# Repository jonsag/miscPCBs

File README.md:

# miscPCBs

A collection of own designed PCBs.  

## 2PinLCDBackPack

Interface and Arduino to an HD4470 LCD using the I2C protocol.  
Uses an PCF8574 I2C I/O bus expander.  

## 3PinLCDBackpack

Interface an Arduino to an HD4470 LCD with 3 pins instead of 6.  
Using the 74HC595 8-bit shift register with output latches.  

## 8PinLCDBackPack

## FM-Transmitter

A miniaturized FM transmitter.  

## LCDBackPack

The default way to control the HD4470 LCD.  

## medzik TDA2005 Amplifier

A basic amplifier using the 2-channel TDA2005.  

## rotaryToolMotorController

Schematics of a Dremel 3000 motor control.  

## TDA2005-amplifiers

1-channel bridged amplifier using TDA2005.  
2-channel amplifier with tone, balance and loudness control. Also with TDA2005.  

## TDA2005R

An amplifier with PCB layout possible to etch at home.  
Uses TDA2005.  

## Uber I2C LCD Controller Module

Even more control over the LCD.

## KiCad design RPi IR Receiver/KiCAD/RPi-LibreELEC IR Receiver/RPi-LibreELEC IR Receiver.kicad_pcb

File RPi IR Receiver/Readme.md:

# RPi/LibreELEC IR Receiver

## Software

Edit config  

>$ mount -o remount,rw /flash  
>$ nano /flash/config.txt  

Uncomment  'dtoverlay=gpio-ir,gpio_pin=18' so that  

    # uncomment to enable infrared remote receiver connected to GPIO 18
    dtoverlay=gpio-ir,gpio_pin=18

>$ mount -o remount,ro /flash  
>$ reboot  

### If you have a Hauppauge remote

    /storage/.config/rc_maps.cfg  

    /storage/.config/rc_keymaps/hauppauge  

## Testing

To test a different keytable file run  

>$ ir-keytable -c -w /path/to/keytable-file

For example  

>$ ir-keytable -c -w /usr/lib/udev/rc_keymaps/samsung

If the output ends with these lines the protocol is not supported by the IR receiver  

    Invalid protocols selected
    Couldn't change the IR protocols

## Creating own keytable

From [https://wiki.libreelec.tv/configuration/ir-remotes](https://wiki.libreelec.tv/configuration/ir-remotes)  

If you cannot find a working keymap or the current keymap has missing buttons you can create your own.  

Stop Kodi  

>$ systemctl stop kodi  
>$ systemctl stop eventlircd

Run  

>$ ir-keytable

to find out which protocols the receiver driver supports. Look at the 'Supported protocols'  

    Found /sys/class/rc/rc0/ (/dev/input/event1) with:
            Driver gpio-rc-recv, table rc-rc6-mce
            Supported protocols: lirc rc-5 rc-5-sz jvc sony nec sanyo mce_kbd rc-6 sharp xmp
            Enabled protocols: lirc nec rc-6
            Name: gpio_ir_recv
            bus: 25, vendor/product: 0001:0001, version: 0x0100
            Repeat delay = 500 ms, repeat period = 125 ms

Run  

>$ ir-keytable -p \<PROTOCOL\> -t

and press buttons on the remote. If you discover the correct protocol you will see EV_MSC events and the scancode of the button pressed  

    Protocols changed to rc-5
    Testing events. Please, press CTRL-C to abort.
    1503592437.660155: event type EV_MSC(0x04): scancode = 0x101a
    1503592437.660155: event type EV_SYN(0x00).
    1503592437.774129: event type EV_MSC(0x04): scancode = 0x101a
    1503592437.774129: event type EV_SYN(0x00).
    1503592437.921009: event type EV_MSC(0x04): scancode = 0x101a

If you see no events stop ir-keytable with CTRL-C and try another protocol from the list. You can ignore lirc as this is not a real protocol.  

Once you find the correct IR protocol create  

    /storage/.config/rc_keymaps/custom_remote
    
and set the header file. In the example above the protocol is rc-5 so we set  

    # table custom_remote, type: rc-5

Now build the keytable file  

>$ nano /storage/.config/rc_keymaps/custom_remote

Run  

>$ ir-keytable -t

to find out the scancode of each button.  
For each button do the following:  

* Press a button and note the scancode (the 0x… value after scancode:)

* Add a new line with the scancode (including 0x).

* Add the Linux keycode in "quoted" format and separated with a blank.

You can get a list of all supported Linux keycodes via  

>$ irrecord -l | grep ^KEY

but it is easiest to use keycodes listed in the  

    <remote device=“devinput”>
    
section of  

    /usr/share/kodi/system/Lircmap.xml

Once you are finished with the keytable, save the file, stop ir-keytable -t with CTRL-C and then restart it with the keytable file  

>$ ir-keytable -c -w /storage/.config/rc_keymaps/custom_remote

    Read justboom table
    Old keytable cleared
    Wrote 12 keycode(s) to driver
    Protocols changed to rc-5

Now run  

>$ ir-keytable -t

and press buttons  

    Testing events. Please, press CTRL-C to abort.
    1503599395.150849: event type EV_MSC(0x04): scancode = 0x1019
    1503599395.150849: event type EV_KEY(0x01) key_down: KEY_VOLUMEUP(0x0073)
    1503599395.150849: event type EV_SYN(0x00).
    1503599395.264827: event type EV_MSC(0x04): scancode = 0x1019
    1503599395.264827: event type EV_SYN(0x00).
    1503599395.413668: event type EV_MSC(0x04): scancode = 0x1019
    1503599395.413668: event type EV_SYN(0x00).
    1503599395.673626: event type EV_KEY(0x01) key_up: KEY_VOLUMEUP(0x0073)
    1503599395.673626: event type EV_SYN(0x00).

If the test is successful, make the keytable persistent by creating  

    /storage/.config/rc_maps.cfg
    
with the following content:  

    * * custom_remote

Reboot and you should have a working remote in Kodi  

## Links

* [Using an IR Remote with a Raspberry Pi Media Center](https://learn.adafruit.com/using-an-ir-remote-with-a-raspberry-pi-media-center/hardware)
* [Add Infrared Interface to Your Raspberry Pi GPIO](https://www.instructables.com/Add-Infrared-Interface-to-Your-Raspberry-Pi/)
* [How to Send and Receive IR Signals with a Raspberry PiT](https://www.digikey.se/sv/maker/tutorials/2021/how-to-send-and-receive-ir-signals-with-a-raspberry-pi?srsltid=AfmBOorkv28s5m4hSEOjsUYEw9_w3052pLwMHnE4Wjwx3rge6P-vsTNT)
* [TSOP38238  IR-Receiver 38kHz](https://www.electrokit.com/tsop38238-ir-mottagare-38khz)

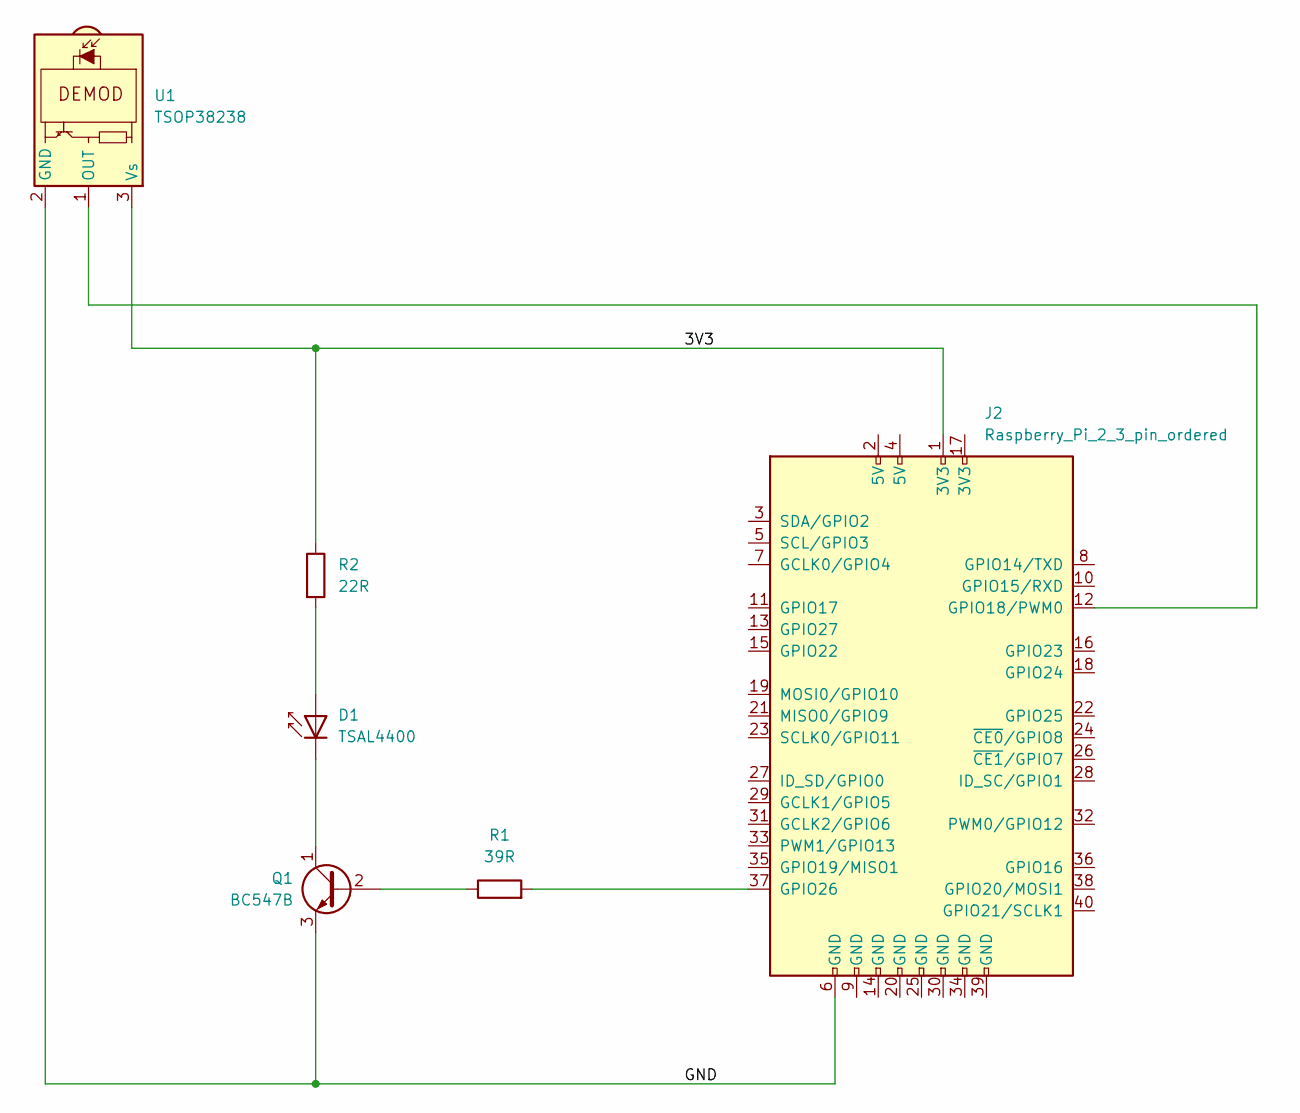
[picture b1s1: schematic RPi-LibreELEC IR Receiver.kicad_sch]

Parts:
D1: TSAL4400; LED_D3.0mm_IRBlack
J2: Raspberry_Pi_2_3_pin_ordered; RaspberryPi_Hat_2x20_pin_GPIO_larger_pads
Q1: BC547B; TO-92_Inline_Wide_large
R1: 39R; R_Axial_DIN0207_L6.3mm_D2.5mm_P10.16mm_Horizontal_large
R2: 22R; R_Axial_DIN0207_L6.3mm_D2.5mm_P10.16mm_Horizontal_large
U1: TSOP38238; Vishay_MINICAST-3Pin

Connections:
/3V3: J2.1 (3V3), R2.1, U1.3 (Vs)
/GND: J2.6 (GND), Q1.3 (E), U1.2 (GND)
unnamed: D1.2 (A), R2.2
unnamed: D1.1 (K), Q1.1 (C)
unnamed: J2.12 (GPIO18/PWM0), U1.1 (OUT)
unnamed: J2.37 (GPIO26), R1.2
unnamed: Q1.2 (B), R1.1

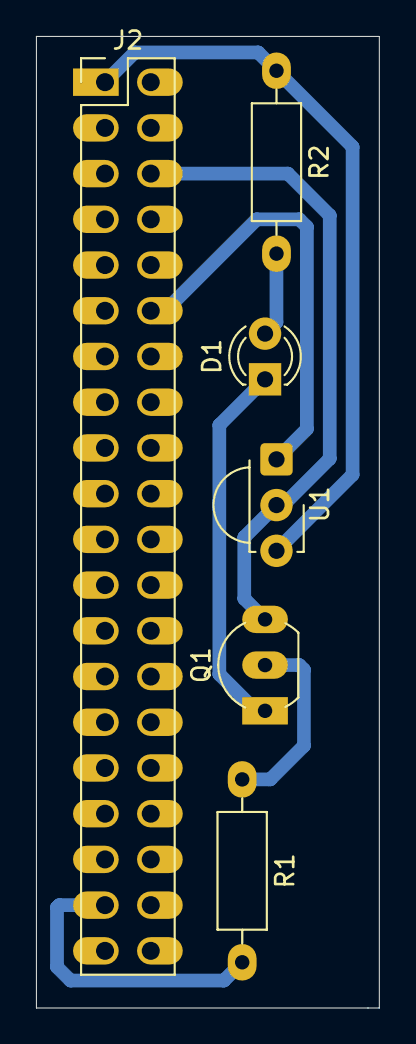
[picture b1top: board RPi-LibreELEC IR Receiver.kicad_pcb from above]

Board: 2 copper layers, 19.0 x 54.0 mm, 6 parts (0 on the bottom side), 7 nets.

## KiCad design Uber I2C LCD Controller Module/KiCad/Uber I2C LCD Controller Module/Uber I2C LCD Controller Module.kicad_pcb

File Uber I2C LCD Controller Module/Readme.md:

# Uber I2C LCD Controller Module

## Links

* [https://www.instructables.com/I2C-LCD-Controller-Module/](https://www.instructables.com/I2C-LCD-Controller-Module/)
* [https://github.com/SteveQuinn1/LiquidCrystal_I2C_PCF8574](https://github.com/SteveQuinn1/LiquidCrystal_I2C_PCF8574)
* [https://github.com/SteveQuinn1/MCP4561_DIGI_POT](https://github.com/SteveQuinn1/MCP4561_DIGI_POT)

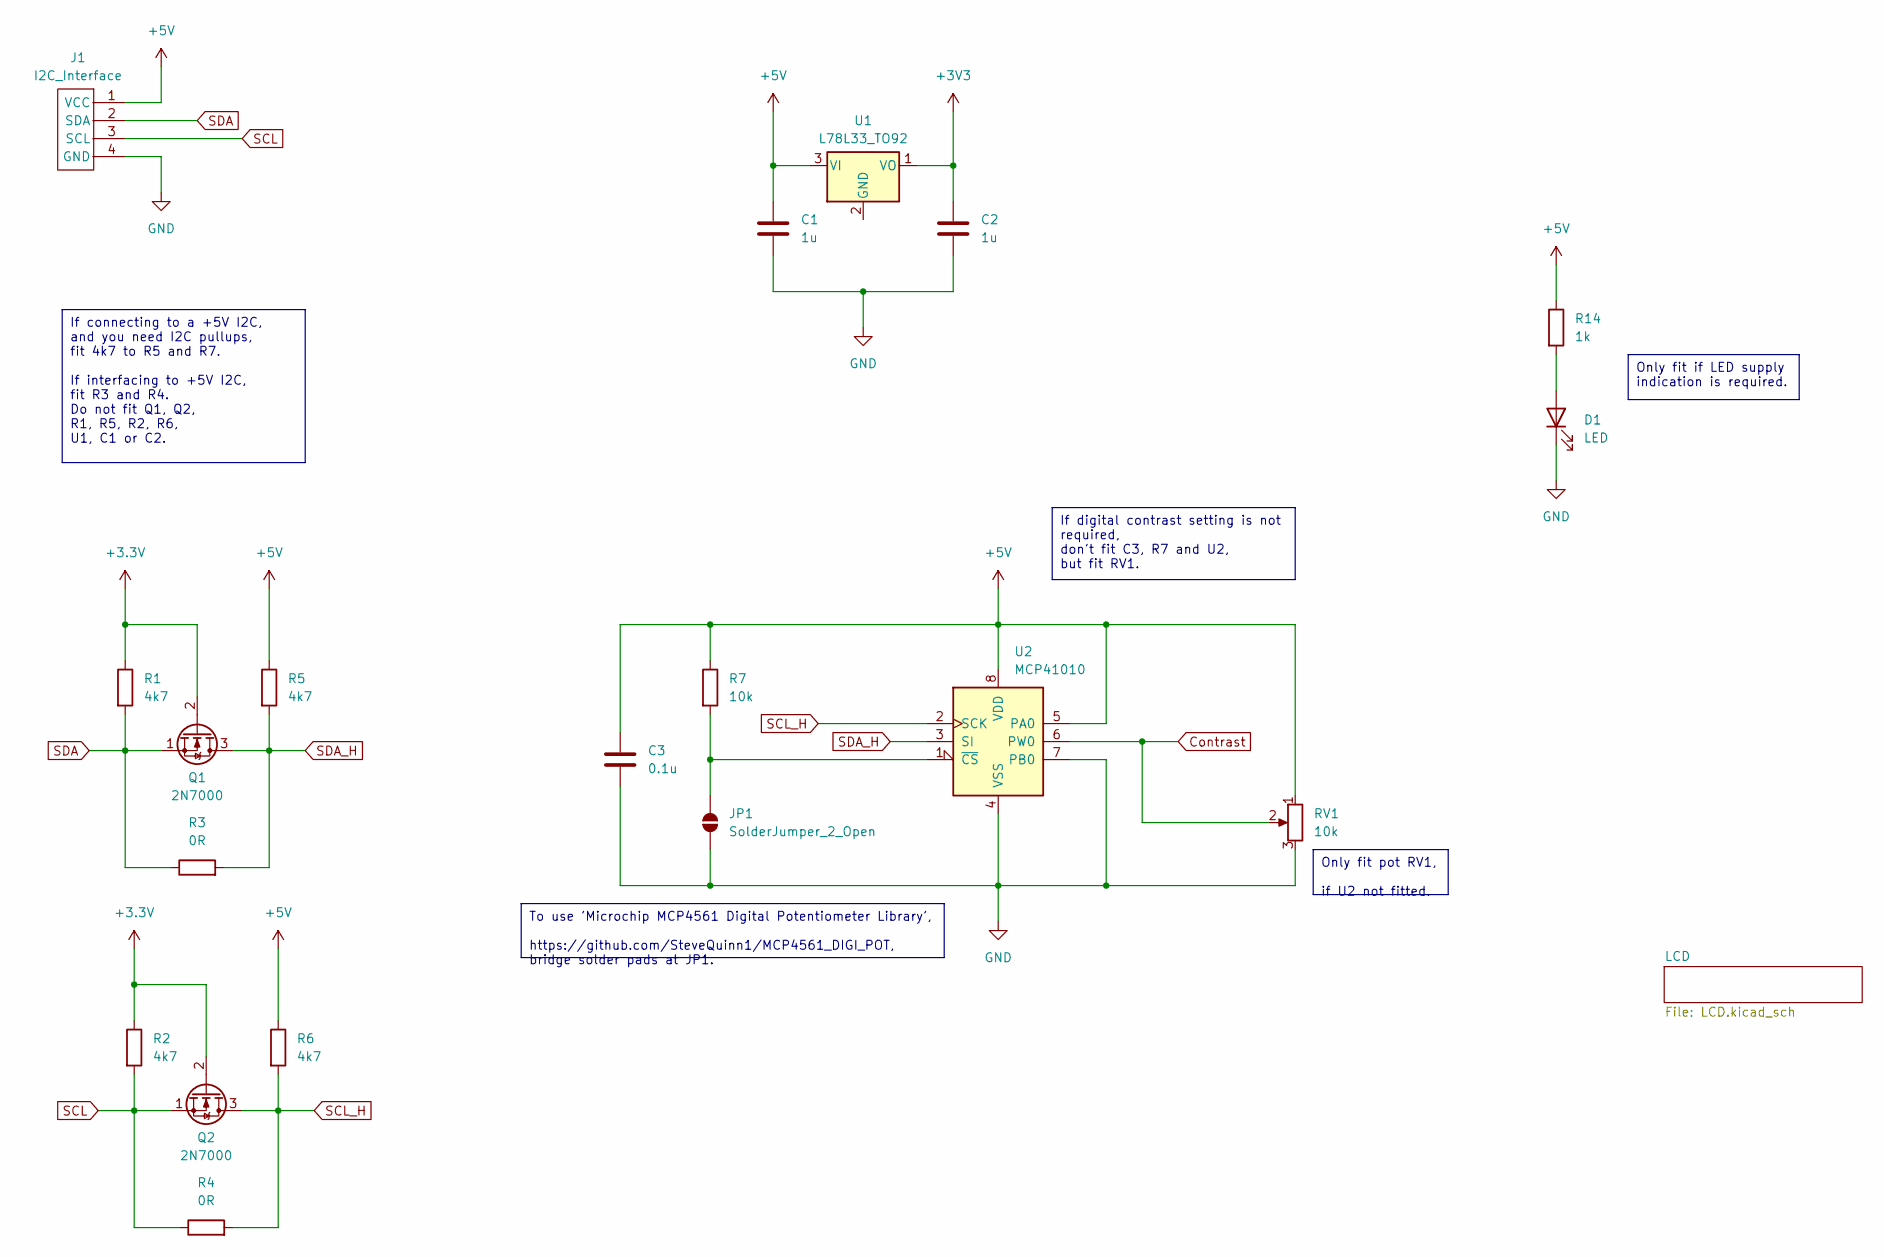
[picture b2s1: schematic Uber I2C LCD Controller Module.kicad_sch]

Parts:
C1, C2: 1u; C_Disc_D3.0mm_W1.6mm_P2.50mm_larg
C3: 0.1u; C_Disc_D3.0mm_W1.6mm_P2.50mm_larg
D1: LED; LED_D5.0mm_large
J1: I2C_Interface; 4-pin JST I2C
JP1: SolderJumper_2_Open; SolderJumper-2_P1.3mm_Open_Pad1.0x1.5mm
Q1, Q2: 2N7000; TO-92_Inline
R1, R2, R5, R6: 4k7; R_Axial_DIN0207_L6.3mm_D2.5mm_P10.16mm_Horizontal_large
R3, R4: 0R; R_Axial_DIN0207_L6.3mm_D2.5mm_P10.16mm_Horizontal_large
R7: 10k; R_Axial_DIN0207_L6.3mm_D2.5mm_P10.16mm_Horizontal_large
R14: 1k; R_Axial_DIN0207_L6.3mm_D2.5mm_P10.16mm_Horizontal_large
RV1: 10k; Potentiometer_Bourns_3339P_Vertical_large
U1: L78L33_TO92; TO-92_Inline
U2: MCP41010; DIP-8_W7.62mm_Socket_w_dip_packet_LongPads

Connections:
+3.3V: Q1.2 (G), Q2.2 (G), R1.1, R2.1
+3V3: C2.1, U1.1 (VO)
+5V: C1.1, C3.1, J1.1 (VCC), R5.1, R6.1, R7.1, R14.1, RV1.1, U1.3 (VI), U2.5 (PA0), U2.8 (VDD); also elsewhere on the board
Contrast: RV1.2, U2.6 (PW0); also elsewhere on the board
GND: C1.2, C2.2, C3.2, D1.1 (K), J1.4 (GND), JP1.1 (A), RV1.3, U2.4 (VSS), U2.7 (PB0); also elsewhere on the board
unnamed: D1.2 (A), R14.2
unnamed: JP1.2 (B), R7.2, U2.1 (~CS)
SCL: J1.3 (SCL), Q2.1 (S), R2.2, R4.1
SCL_H: Q2.3 (D), R4.2, R6.2, U2.2 (SCK); also elsewhere on the board
SDA: J1.2 (SDA), Q1.1 (S), R1.2, R3.1
SDA_H: Q1.3 (D), R3.2, R5.2, U2.3 (SI); also elsewhere on the board

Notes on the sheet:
If digital contrast setting is not required, don't fit C3, R7 and U2, but fit RV1.
Only fit if LED supply indication is required.
To use 'Microchip MCP4561 Digital Potentiometer Library', https://github.com/SteveQuinn1/MCP4561_DIGI_POT, bridge solder pads at JP1.
Only fit pot RV1, if U2 not fitted.
If connecting to a +5V I2C, and you need I2C pullups, fit 4k7 to R5 and R7. If interfacing to +5V I2C, fit R3 and R4. Do not fit Q1, Q2, R1, R5, R2, R6, U1, C1 or C2.

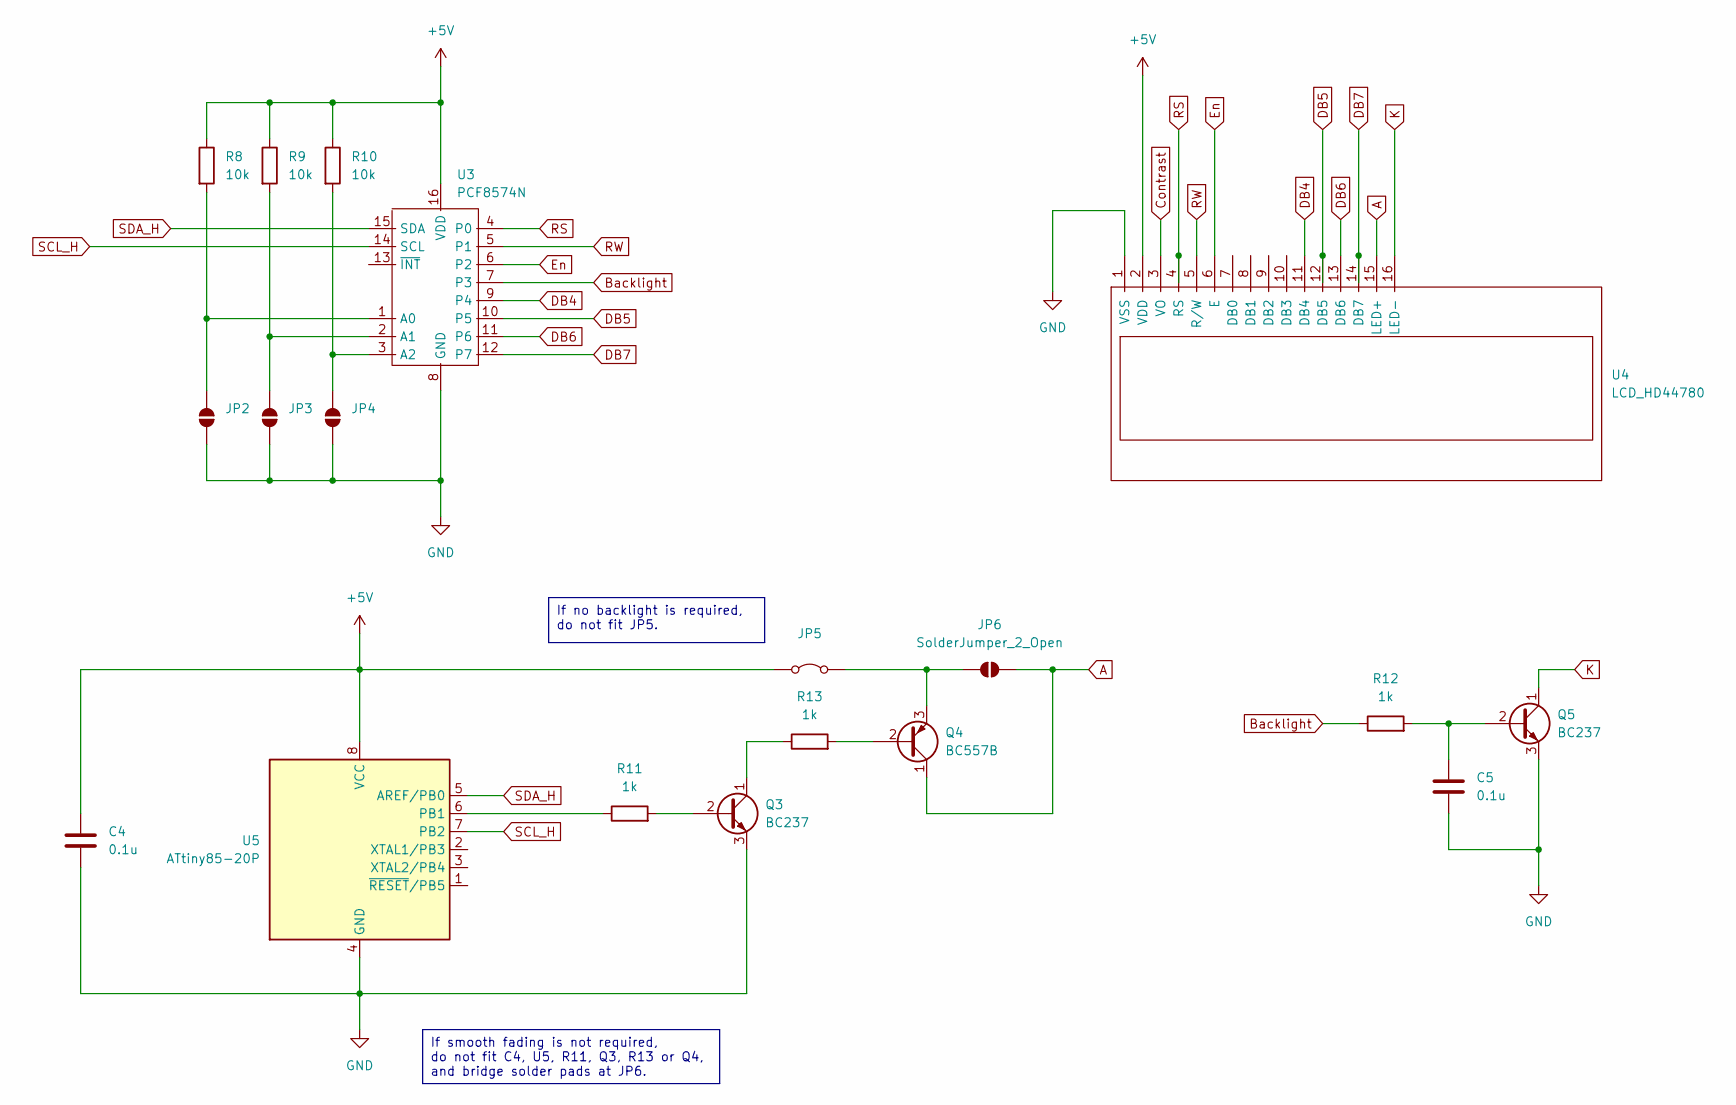
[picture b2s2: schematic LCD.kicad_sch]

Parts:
C4, C5: 0.1u; C_Disc_D3.0mm_W1.6mm_P2.50mm_larg
JP2, JP3, JP4, JP6: SolderJumper_2_Open; SolderJumper-2_P1.3mm_Open_Pad1.0x1.5mm
JP5: Jumper_2_Bridged; PinSocket_1x02_P2.54mm_Vertical
Q3, Q5: BC237; TO-92_Inline
Q4: BC557B; TO-92_Inline
R8, R9, R10: 10k; R_Axial_DIN0207_L6.3mm_D2.5mm_P10.16mm_Horizontal_large
R11, R12, R13: 1k; R_Axial_DIN0207_L6.3mm_D2.5mm_P10.16mm_Horizontal_large
U3: PCF8574N; DIP-16_W7.62mm_w socket
U4: LCD_HD44780; LCD_HD44780_16x2_w_headers_large
U5: ATtiny85-20P; DIP-8_W7.62mm_Socket_w_dip_packet_LongPads

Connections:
+5V: C4.1, JP5.1 (A), R8.1, R9.1, R10.1, U3.16 (VDD), U4.2 (VDD), U5.8 (VCC); also elsewhere on the board
A: JP6.2 (B), Q4.1 (C), U4.15 (LED+)
Backlight: R12.1, U3.7 (P3)
Contrast: U4.3 (VO); also elsewhere on the board
DB4: U3.9 (P4), U4.11 (DB4)
DB5: U3.10 (P5), U4.12 (DB5)
DB6: U3.11 (P6), U4.13 (DB6)
DB7: U3.12 (P7), U4.14 (DB7)
En: U3.6 (P2), U4.6 (E)
GND: C4.2, C5.2, JP2.1 (A), JP3.1 (A), JP4.1 (A), Q3.3 (E), Q5.3 (E), U3.8 (GND), U4.1 (VSS), U5.4 (GND); also elsewhere on the board
K: Q5.1 (C), U4.16 (LED-)
unnamed: JP2.2 (B), R8.2, U3.1 (A0)
unnamed: JP3.2 (B), R9.2, U3.2 (A1)
unnamed: JP4.2 (B), R10.2, U3.3 (A2)
unnamed: JP5.2 (B), JP6.1 (A), Q4.3 (E)
unnamed: Q3.2 (B), R11.2
unnamed: Q3.1 (C), R13.1
unnamed: Q4.2 (B), R13.2
unnamed: C5.1, Q5.2 (B), R12.2
unnamed: R11.1, U5.6 (PB1)
RS: U3.4 (P0), U4.4 (RS)
RW: U3.5 (P1), U4.5 (R/W)
SCL_H: U3.14 (SCL), U5.7 (PB2); also elsewhere on the board
SDA_H: U3.15 (SDA), U5.5 (AREF/PB0); also elsewhere on the board

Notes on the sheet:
If no backlight is required, do not fit JP5.
If smooth fading is not required, do not fit C4, U5, R11, Q3, R13 or Q4, and bridge solder pads at JP6.

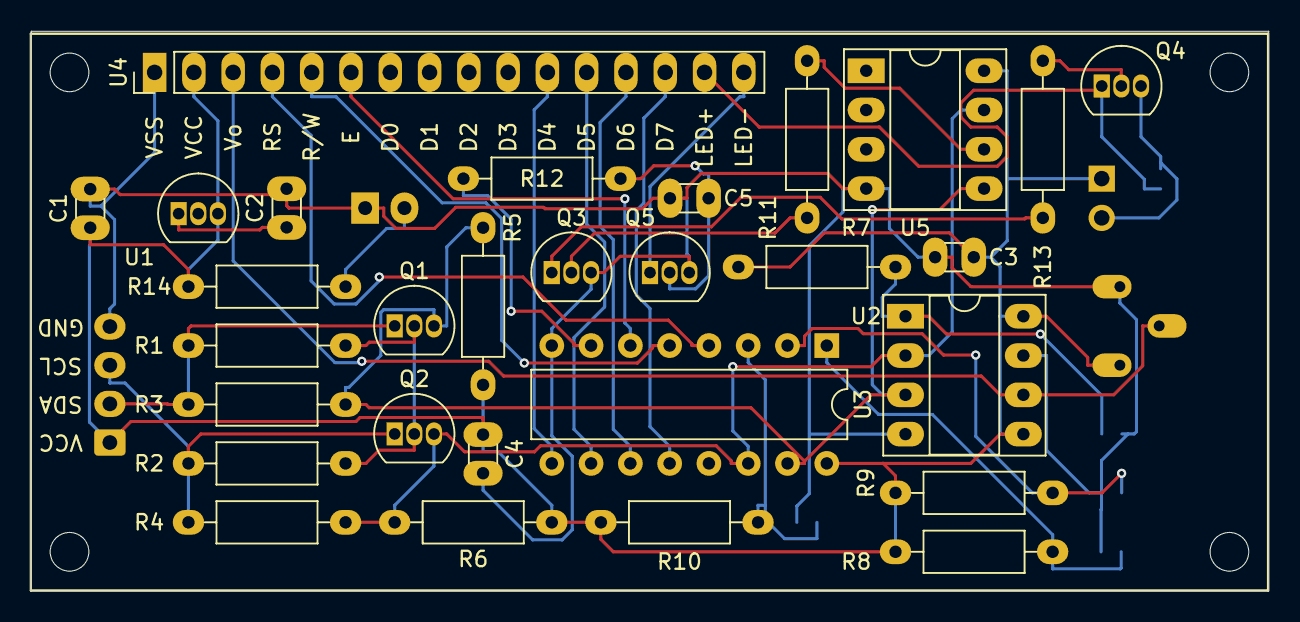
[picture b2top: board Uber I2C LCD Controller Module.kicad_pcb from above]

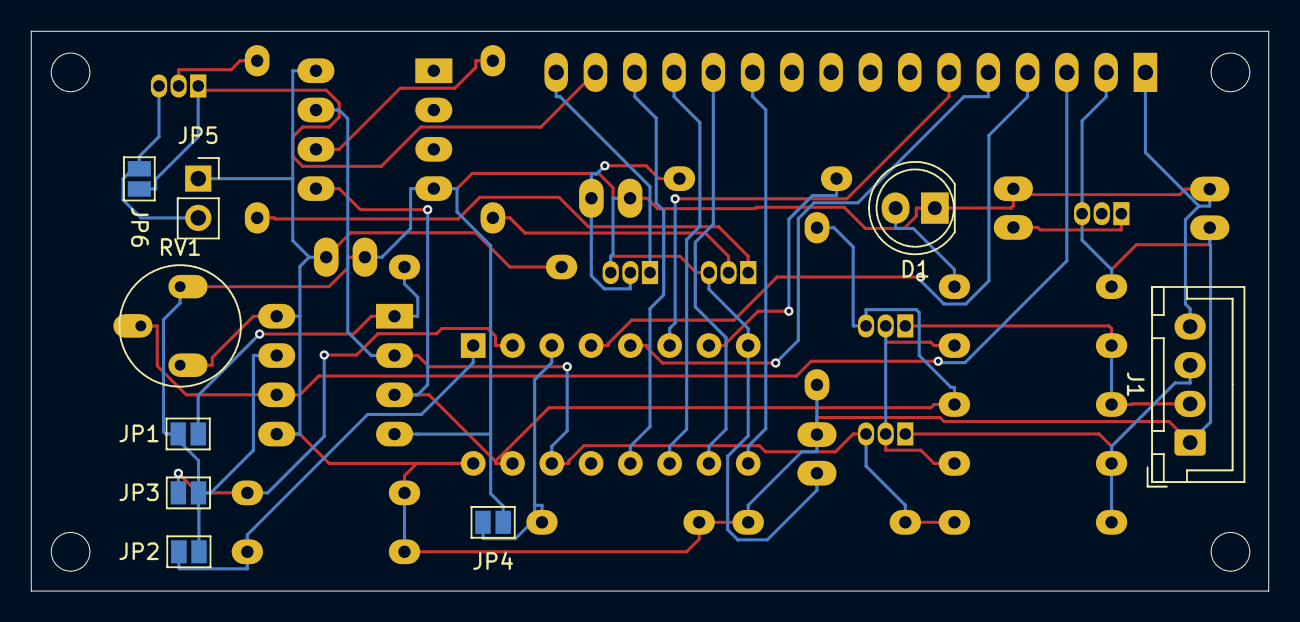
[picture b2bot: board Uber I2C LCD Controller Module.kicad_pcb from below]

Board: 2 copper layers, 80.0 x 36.2 mm, 38 parts (9 on the bottom side), 30 nets.

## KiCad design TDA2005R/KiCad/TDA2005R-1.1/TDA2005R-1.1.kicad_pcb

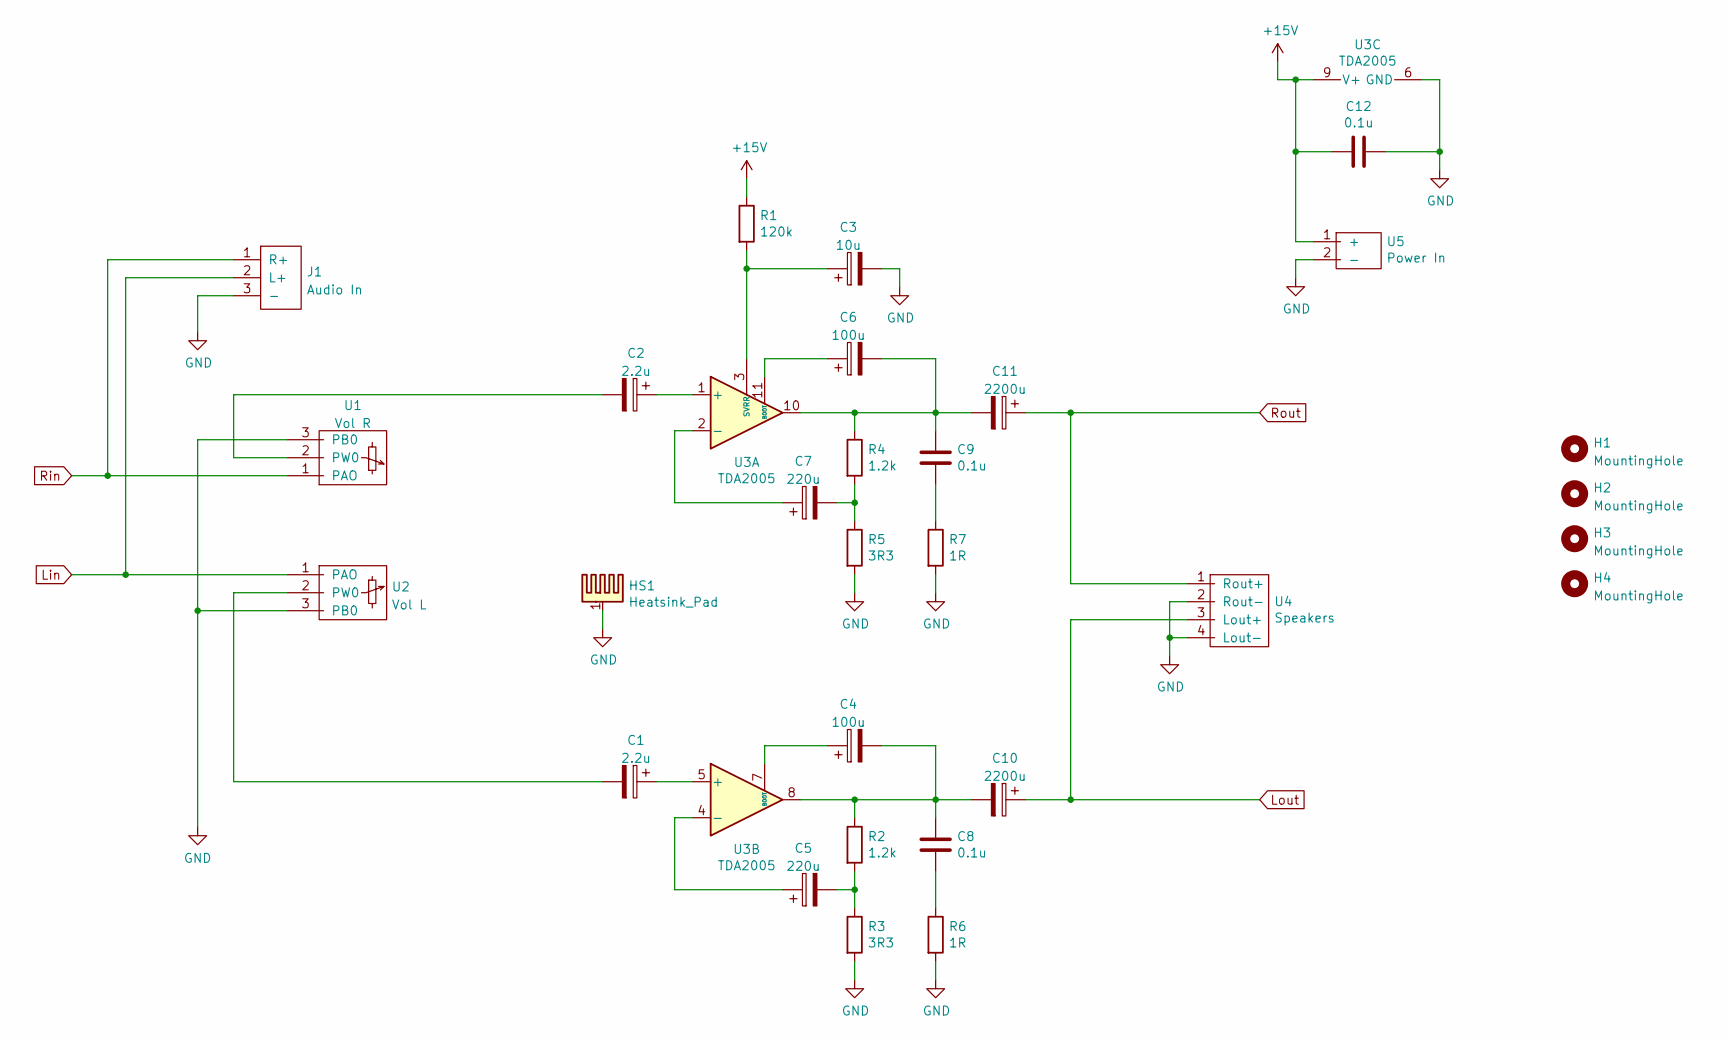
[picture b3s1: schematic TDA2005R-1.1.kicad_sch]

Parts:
C1, C2: 2.2u; CP_Radial_D5.0mm_P2.00mm_larger
C3: 10u; CP_Radial_D5.0mm_P2.00mm_larger
C4, C6: 100u; CP_Radial_D5.0mm_P2.50mm_larger_pads
C5, C7: 220u; CP_Radial_D8.0mm_P3.50mm_large
C8, C9, C12: 0.1u; C_Disc_D7.5mm_W2.5mm_P5.00mm_larger
C10, C11: 2200u; CP_Radial_D13.0mm_P5.00mm_larger
H1, H2, H3, H4: MountingHole; MountingHole_3.2mm_M3
HS1: Heatsink_Pad; EK-41002859
J1: Audio In; 3-pin JST Audio
R1: 120k; R_Axial_DIN0414_L11.9mm_D4.5mm_P15.24mm_Horizontal_larger
R2, R4: 1.2k; R_Axial_DIN0414_L11.9mm_D4.5mm_P15.24mm_Horizontal_larger
R3, R5: 3R3; R_Axial_DIN0414_L11.9mm_D4.5mm_P15.24mm_Horizontal_larger
R6, R7: 1R; R_Axial_DIN0414_L11.9mm_D4.5mm_P15.24mm_Horizontal_larger
U1: Vol R; 3-pin JST Potentiometer
U2: Vol L; 3-pin JST Potentiometer
U3: TDA2005; TO-220-11_P3.4x5.08mm_StaggerOdd_Lead4.85mm_Vertical_large
U4: Speakers; 4-pole_screw_terminal_RL_output
U5: Power In; 2-pole_power_in_screw_terminal

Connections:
+15V: C12.2, R1.1, U3.9 (V+), U5.1 (+)
GND: C3.2, C12.1, HS1.1, J1.3 (-), R3.2, R5.2, R6.2, R7.2, U1.3 (PB0), U2.3 (PB0), U3.6 (GND), U4.2 (Rout-), U4.4 (Lout-), U5.2 (-)
Lin: J1.2 (L+), U2.1 (PAO)
Lout: C10.1, U4.3 (Lout+)
unnamed: C1.1, U3.5 (+)
unnamed: C1.2, U2.2 (PW0)
unnamed: C2.1, U3.1 (+)
unnamed: C2.2, U1.2 (PW0)
unnamed: C3.1, R1.2, U3.3 (SVRR)
unnamed: C4.1, U3.7 (BOOT)
unnamed: C5.1, U3.4 (-)
unnamed: C5.2, R2.2, R3.1
unnamed: C6.1, U3.11 (BOOT)
unnamed: C7.1, U3.2 (-)
unnamed: C7.2, R4.2, R5.1
unnamed: C8.2, R6.1
unnamed: C9.2, R7.1
unnamed: C4.2, C8.1, C10.2, R2.1, U3.8
unnamed: C6.2, C9.1, C11.2, R4.1, U3.10
Rin: J1.1 (R+), U1.1 (PAO)
Rout: C11.1, U4.1 (Rout+)

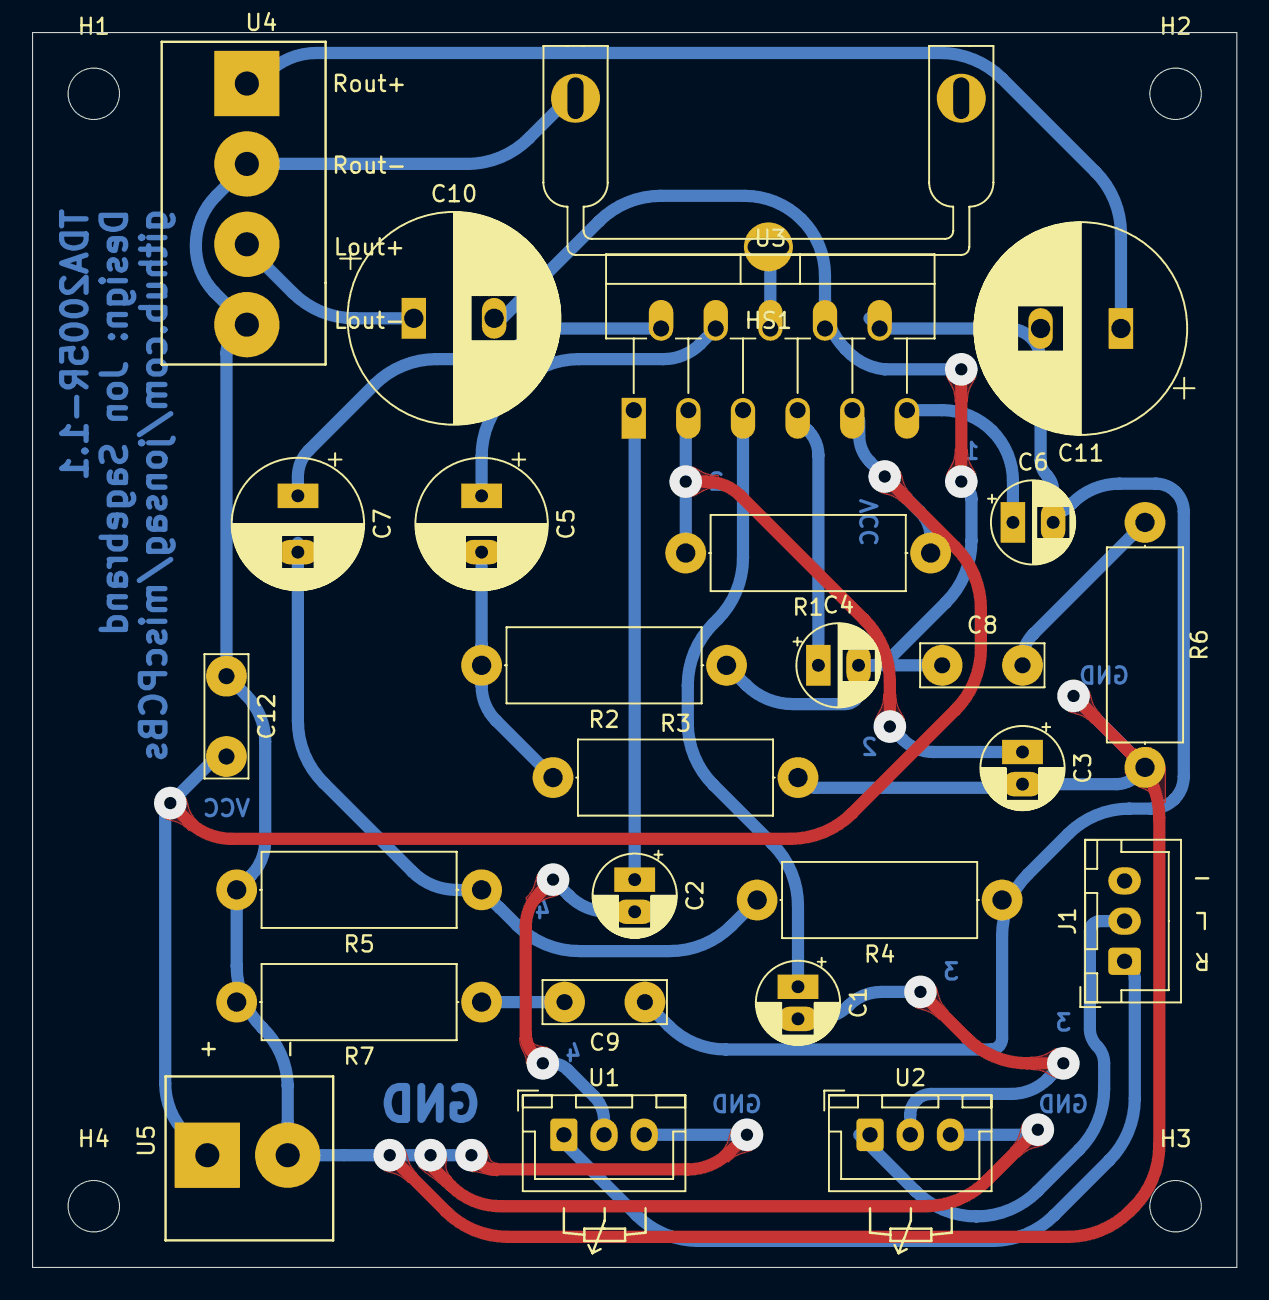
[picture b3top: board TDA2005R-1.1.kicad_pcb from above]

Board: 2 copper layers, 74.9 x 76.8 mm, 30 parts (0 on the bottom side), 21 nets.

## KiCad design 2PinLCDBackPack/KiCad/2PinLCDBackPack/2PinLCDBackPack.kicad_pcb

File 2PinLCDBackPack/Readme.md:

# 2PinLCDBackPack

An I2C interface to an HD4470 LCD

## Links

* [https://forum.arduino.cc/t/connecting-an-hd4470-character-lcd-to-an-mcu-or-arduino-using-just-two-wires/589237](https://forum.arduino.cc/t/connecting-an-hd4470-character-lcd-to-an-mcu-or-arduino-using-just-two-wires/589237)
* [https://www.electrokit.com/pcf8574n-dip-16-i2c-i/o-bus-expander](https://www.electrokit.com/pcf8574n-dip-16-i2c-i/o-bus-expander)
* [https://github.com/mathertel/LiquidCrystal_PCF8574](https://github.com/mathertel/LiquidCrystal_PCF8574)
* [https://www.mathertel.de/Arduino/LiquidCrystal_PCF8574.aspx](https://www.mathertel.de/Arduino/LiquidCrystal_PCF8574.aspx)

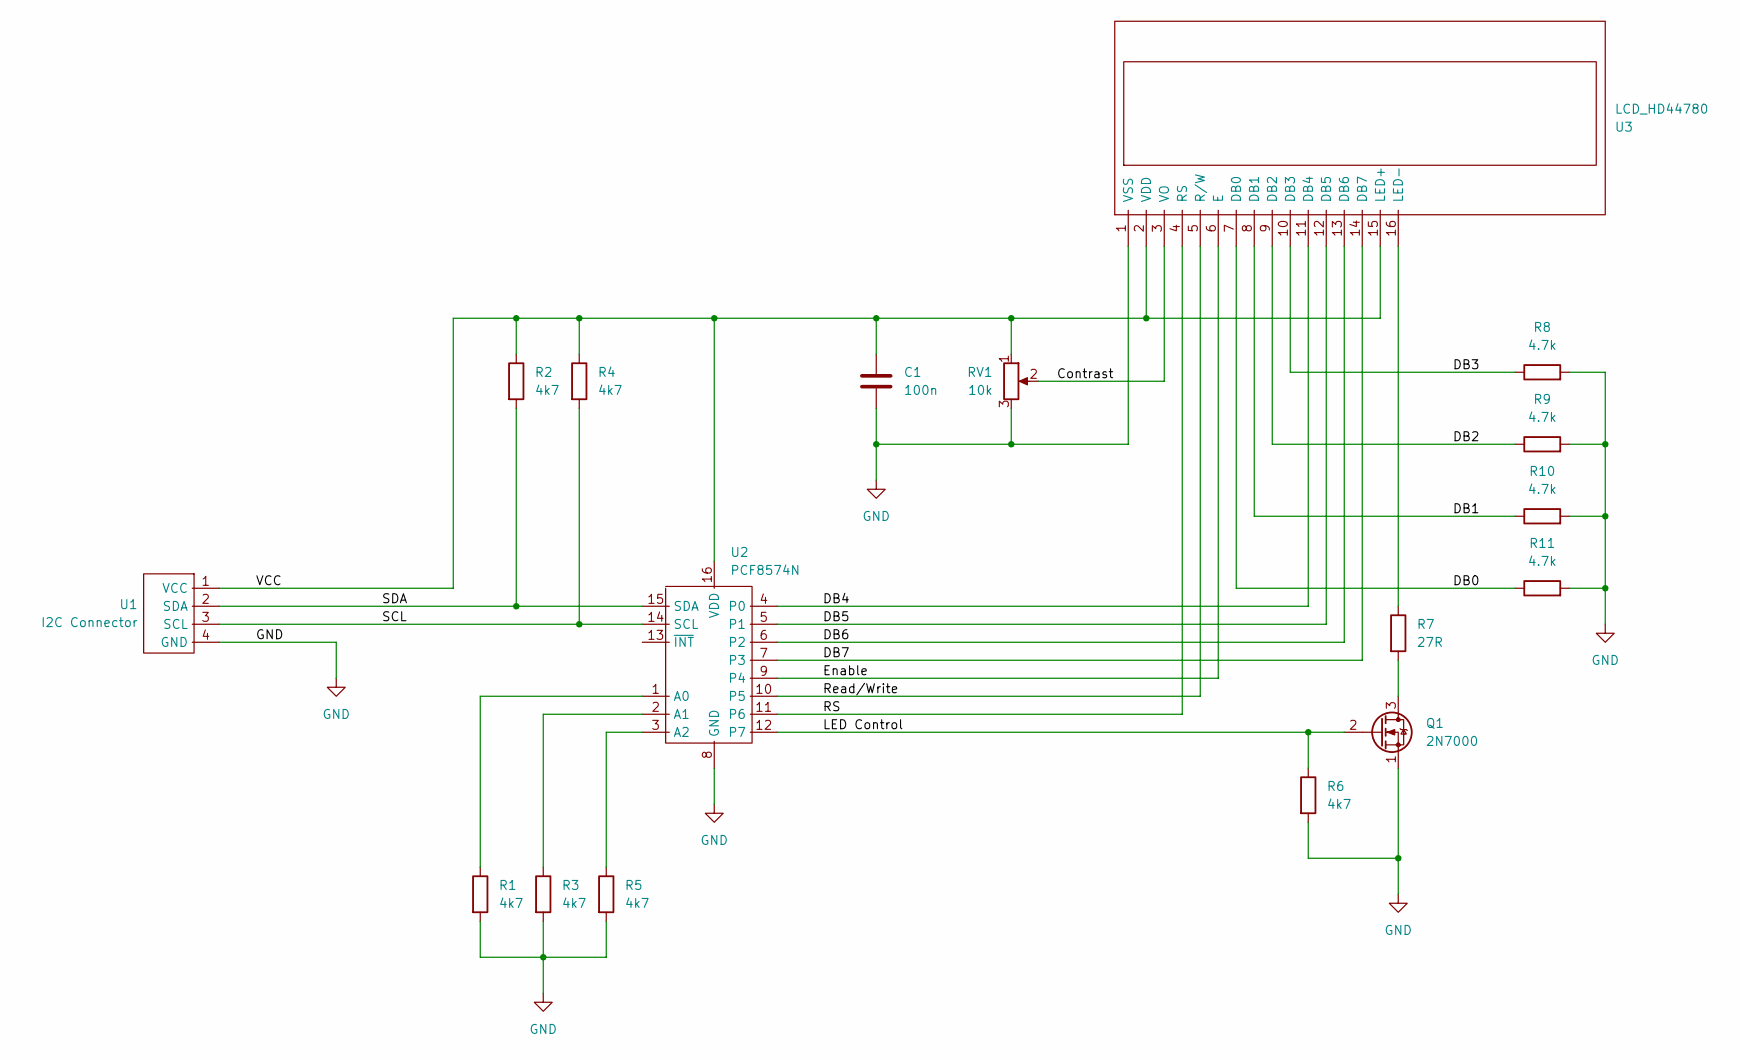
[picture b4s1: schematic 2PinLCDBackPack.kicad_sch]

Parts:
C1: 100n; C_Disc_D3.0mm_W1.6mm_P2.50mm_larg
Q1: 2N7000; TO-92_Inline_Wide_large
R1, R2, R3, R4, R5, R6: 4k7; R_Axial_DIN0207_L6.3mm_D2.5mm_P10.16mm_Horizontal_large
R7: 27R; R_Axial_DIN0207_L6.3mm_D2.5mm_P10.16mm_Horizontal_large
R8, R9, R10, R11: 4.7k; R_Axial_DIN0207_L6.3mm_D2.5mm_P10.16mm_Horizontal_large
RV1: 10k; Potentiometer_Piher_PT-6-V_Vertical_larger_pads
U1: I2C Connector; 4-pin JST I2C
U2: PCF8574N; DIP-16_W7.62mm_w socket
U3: LCD_HD44780; LCD_HD44780_16x2_w_headers_large

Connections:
/Contrast: RV1.2, U3.3 (VO)
/DB0: R11.1, U3.7 (DB0)
/DB1: R10.1, U3.8 (DB1)
/DB2: R9.1, U3.9 (DB2)
/DB3: R8.1, U3.10 (DB3)
/DB4: U2.4 (P0), U3.11 (DB4)
/DB5: U2.5 (P1), U3.12 (DB5)
/DB6: U2.6 (P2), U3.13 (DB6)
/DB7: U2.7 (P3), U3.14 (DB7)
/Enable: U2.9 (P4), U3.6 (E)
/LED Control: Q1.2 (G), R6.1, U2.12 (P7)
/RS: U2.11 (P6), U3.4 (RS)
/Read/Write: U2.10 (P5), U3.5 (R/W)
/SCL: R4.2, U1.3 (SCL), U2.14 (SCL)
/SDA: R2.2, U1.2 (SDA), U2.15 (SDA)
/VCC: C1.1, R2.1, R4.1, RV1.1, U1.1 (VCC), U2.16 (VDD), U3.2 (VDD), U3.15 (LED+)
GND: C1.2, Q1.1 (S), R1.2, R3.2, R5.2, R6.2, R8.2, R9.2, R10.2, R11.2, RV1.3, U1.4 (GND), U2.8 (GND), U3.1 (VSS)
unnamed: Q1.3 (D), R7.2
unnamed: R1.1, U2.1 (A0)
unnamed: R3.1, U2.2 (A1)
unnamed: R5.1, U2.3 (A2)
unnamed: R7.1, U3.16 (LED-)

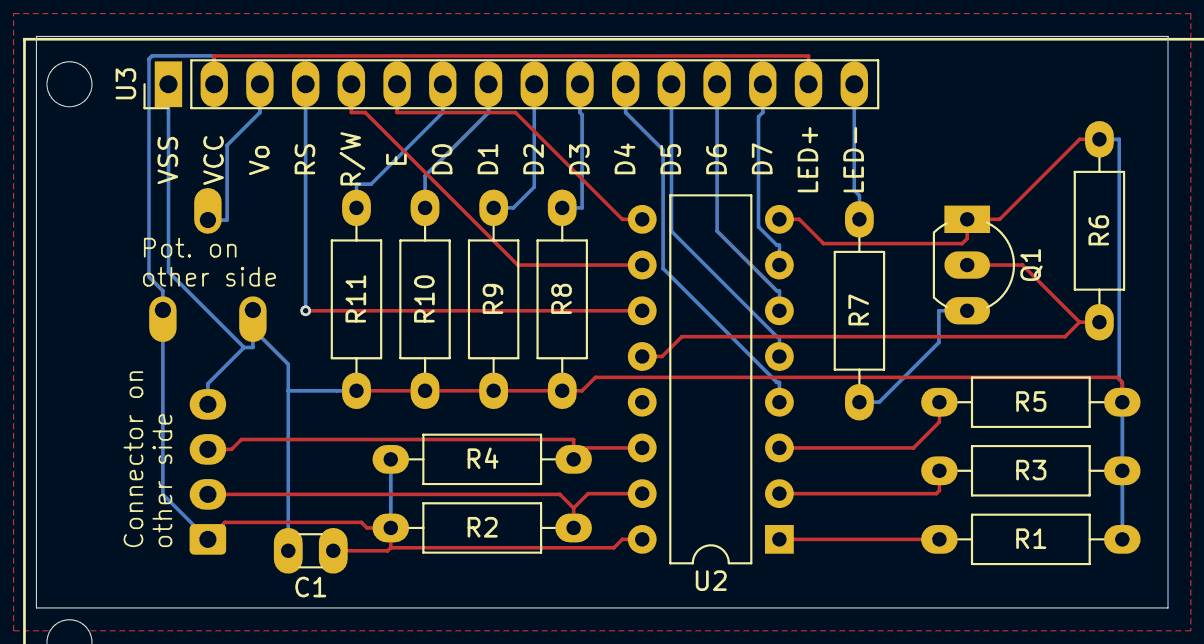
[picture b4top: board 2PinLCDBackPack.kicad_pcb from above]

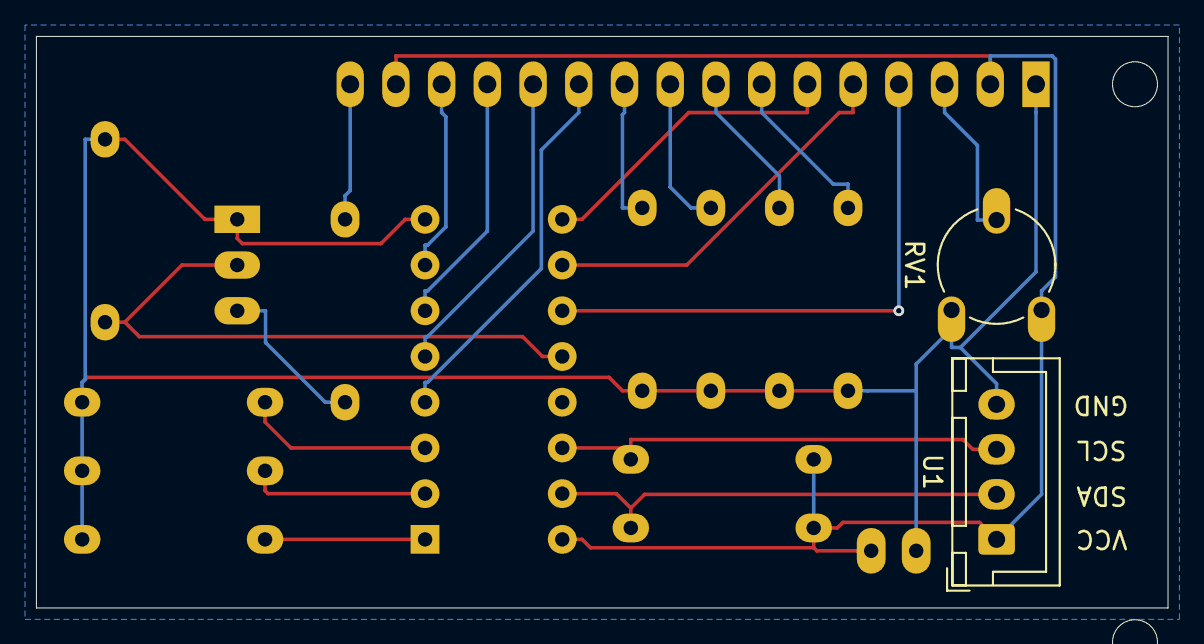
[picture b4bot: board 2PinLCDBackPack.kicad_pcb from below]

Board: 2 copper layers, 62.9 x 31.7 mm, 17 parts (2 on the bottom side), 22 nets.
